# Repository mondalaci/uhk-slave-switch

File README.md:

# UHK Slave Switch

This is a simple switch PCB to easily connect/disconnect the slaves (left keyboard half and add-on modules) of the [Ultimate Hacking Keyboard](https://ultimatehackingkeyboard.com/) for testing purposes.

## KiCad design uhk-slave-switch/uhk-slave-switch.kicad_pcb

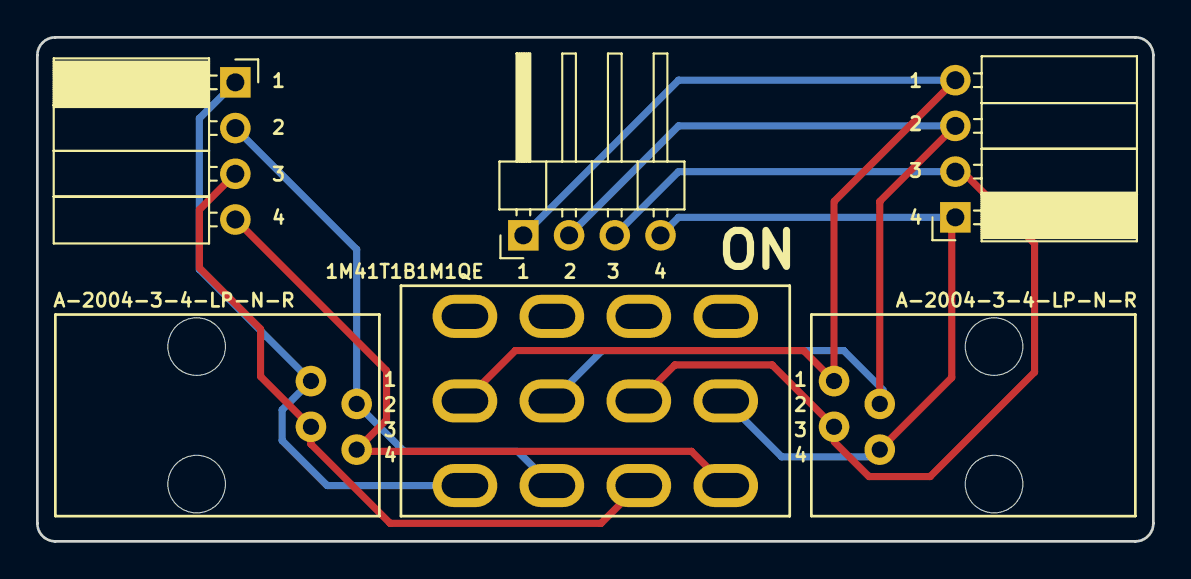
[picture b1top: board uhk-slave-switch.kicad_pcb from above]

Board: 2 copper layers, 62.0 x 28.0 mm, 6 parts (0 on the bottom side), 8 nets.

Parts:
P1, P2: CONN_4; 4P4C_Jack_A-2004-3-4-LP-N-R
P3, P4: CONN_4; Socket_Strip_Angled_1x04_Pitch2.54mm
P5: CONN_4; Pin_Header_Angled_1x04_Pitch2.54mm
SW1: 4P3T; 1M41T1B1M1QE

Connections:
unnamed: P1.1, P3.4, SW1.1
unnamed: P1.2, P3.3, SW1.3
unnamed: P1.3, P3.2, SW1.5
unnamed: P1.4, P3.1, SW1.7
unnamed: P2.1, P4.4, P5.1, SW1.8
unnamed: P2.2, P4.3, P5.2, SW1.6
unnamed: P2.3, P4.2, P5.3, SW1.4
unnamed: P2.4, P4.1, P5.4, SW1.2

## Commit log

2017-09-18 Add board and schematic.
2017-09-18 Reference the latest UGL lib.
2017-09-18 Set output directory to "gerbers".
2017-09-18 Clean up silk screen and enlarge a thin track.
